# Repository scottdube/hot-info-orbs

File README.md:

# HoT Info Orbs

## Quick start: no software to install on your PC

About 10 minutes. You need the built orbs, a **USB-C data cable** (many cheap
cables carry power only), a computer with **Google Chrome or Microsoft Edge**
(Safari and Firefox cannot talk to USB devices), and a **2.4 GHz** WiFi
network.

1. Download the firmware, **[`info_orbs_fw_combo.bin`](https://github.com/scottdube/hot-info-orbs/releases/download/firmware-1.7.0/info_orbs_fw_combo.bin)**
   (click it; it goes to your Downloads folder). It is also on the
   [firmware release page](https://github.com/scottdube/hot-info-orbs/releases/tag/firmware-1.7.0)
   under **Assets**, with its checksum.
2. In Chrome or Edge, open
   **[ESPConnect](https://thelastoutpostworkshop.github.io/ESPConnect/)**.
3. Plug the orbs into the computer with the USB cable. Click **Connect** (top
   left), pick the port that appeared when you plugged in, and click
   **Connect** in that box. On a Mac it is usually *USB JTAG/serial debug
   unit*; on Windows, *USB Serial Device (COM3)* or another COM number.
4. In the left column click **Flash Tools**. Under **Flash Firmware**:
   - **Firmware binary (.bin):** choose `info_orbs_fw_combo.bin`
   - **Flash offset:** `0x0`
   - click **Flash firmware** and wait for it to finish.
5. Unplug the USB cable and plug it back in. The orbs restart.
6. **WiFi:** the screens show a network named `Info-Orbs_` and two
   characters. Join it on a phone; a setup page opens (if not, browse to
   `http://192.168.4.1`). Pick your home WiFi and type its password.
7. **Your free weather key and time zone:** the orbs show their **IP
   address** when they join your WiFi. On a phone or computer on the same
   WiFi, browse to `http://<that address>/settings`. The page starts with
   **API keys**: paste a [Visual Crossing](https://www.visualcrossing.com/sign-up)
   key, free and about a minute to get. Under **Time zone and location**,
   pick your time zone from the list (it starts on New York; daylight saving
   is automatic) and set your weather town, then press **Save and restart**.
   Until the key is in, the weather page stays empty; the clock works without
   it. Own a Tempest weather station? Its token goes under **API keys** too
   ([details](docs/USER-GUIDE.md#weather-from-your-own-tempest-stations)).

**Connect finds no port?** Put the XIAO in download mode: unplug, hold the
**B** button on the XIAO, plug back in, let go, and click **Connect** again.
Anything else: [Troubleshooting](docs/TROUBLESHOOTING.md).

**Running? Next:** the [user guide](docs/USER-GUIDE.md) covers the buttons,
the pages, the settings page and what the orbs do when WiFi drops.

## Updating later: over WiFi, no cable

After the first install, new versions go in over WiFi with a second, smaller
file, `firmware.bin`. It replaces only the software and keeps your WiFi, key,
settings and start-up picture.

1. Download **[`firmware.bin`](https://github.com/scottdube/hot-info-orbs/releases/download/firmware-1.7.0/firmware.bin)**.
2. On a phone or computer on the same WiFi, browse to
   `http://<orbs' address>/update` (the address the orbs show at start-up).
3. Choose `firmware.bin` and press **Upload**. The orbs restart on their own
   when it is done, with your WiFi, key and settings kept.

**Update failed, or the orbs stay dark?** Nothing is broken: do the
[Quick start](#quick-start-no-software-to-install-on-your-pc) again. It wipes
the board, so WiFi and the weather key go back in at steps 6 and 7.

Want to change the code, or build it yourself? The [build guide](docs/SETUP.md)
covers that.

## Want a more hands-on install? Start here

**You don't need a GitHub account.** The list of folders above is the
project's files. Pick the link that matches what you want:

| You want to… | Go to |
|---|---|
| see what it is and what it does | the [feature sheet](https://scottdube.github.io/hot-info-orbs/features.html), an ordinary web page |
| get a built one running, nothing to install | the [Quick start](#quick-start-no-software-to-install-on-your-pc) above: download one file, flash it from Chrome |
| learn the buttons, the pages and the settings | the [user guide](docs/USER-GUIDE.md) |
| fix something that looks wrong | [Troubleshooting](docs/TROUBLESHOOTING.md), organized by what you see |
| build the software yourself, or change it | the [build guide](docs/SETUP.md), written for someone who has never done this |
| order a bare board | the [board rev 2.5 release](https://github.com/scottdube/hot-info-orbs/releases/tag/board-rev2.5): gerber zip for the fab, parts list, schematic and board PDFs, 3D model |
| print the enclosure | [hardware/enclosures/](hardware/enclosures/): the Winged Speedster enclosure, one `.3mf` per part (they open in Bambu Studio, PrusaSlicer and Orca Slicer), with [how many of each to print](hardware/enclosures/winged-speedster/3mf/README.md), two Bambu Studio projects and the Fusion source |
| get all the source | the green **Code** button above, then **Download ZIP** |

## What it shows

Each page uses all five displays. Set a rotation time (on the settings page,
or `WIDGET_CYCLE_DELAY` in `config.h`) and the orbs move from page to page on
their own. The left and right buttons step back and forward by hand.
Hold the middle button for 2 seconds to see the orb's own info page:
firmware version, WiFi, address, health and data feeds. It appears while
you are still holding. Any button closes it, or it closes by itself after
2 minutes. The [user guide](docs/USER-GUIDE.md) explains every line on it.

- **Clock**: normal, Nixie-tube, or custom faces, in your choice of colors.
- **Weather** for a town (Visual Crossing), from your own
  [Tempest](https://tempest.earth) weather stations (one page per station),
  or both.
- **Stocks**: five tickers.
- **Custom pages** that you set up from the browser, no rebuild:
  - **Web Data** draws a JSON file from any web address.
  - **MQTT**, up to two pages, shows one live value per display from an MQTT
    broker, such as Home Assistant. Long values wrap, and the orbs on a page
    share one text size.

  See [docs/CUSTOM-PAGES.md](docs/CUSTOM-PAGES.md).

## What you need

**To run it** (the [Quick start](#quick-start-no-software-to-install-on-your-pc)):

- The assembled orbs: carrier board, a XIAO ESP32-S3 or S3 Plus, five GC9A01
  round displays, three buttons.
  **S3 or S3 Plus makes no difference to the software.** Both use the same
  file; there is nothing to change. The Plus has more memory, which the
  software does not use yet.
- A **USB data cable**. Many cheap cables carry power only.
- A **2.4 GHz** WiFi network. The ESP32 cannot see 5 GHz.
- A computer with **Google Chrome or Microsoft Edge**, for the first install
  only. After that a phone is enough.
- One free **API key**. An API key is a code a website gives you when you
  sign up, so the orbs can ask it for data. It takes about a minute:
  [Visual Crossing](https://www.visualcrossing.com/sign-up), for weather.
  Sign up for your own. A shared key uses up one free allowance, and if it is
  cancelled it stops working for everyone using it. The time zone needs no
  key: the firmware carries the daylight-saving rules itself.

**To build the software yourself**, also:

- [VS Code](https://code.visualstudio.com) with the
  [PlatformIO](https://platformio.org) extension, and about 1 GB of free
  disk. Most people never need this.

## Using it

Once the orbs are on your WiFi, everything is done from a web browser on a
phone or computer on the same WiFi. The orbs show their **IP address** on
orb 5 when they join (four numbers with dots, like `192.168.1.57`).

| Address | What it does |
|---|---|
| `http://<IP>/settings` | rotation time, which pages show, tickers, weather location and units, time zone, clock face and colors, night dimming, upside-down mounting, the waking eyes at start-up, what to show when WiFi is out, custom pages, your own start-up picture |
| `http://<IP>/update` | install a new version of the software without a cable. The page also shows which version is running. |

The [user guide](docs/USER-GUIDE.md) has the rest: the buttons, each page,
every section of the settings page, the info page, what the amber and red
marks mean, changing WiFi, running from a phone hotspot, and the log.
[Troubleshooting](docs/TROUBLESHOOTING.md) is organized by what you see.

## Building it yourself

[docs/SETUP.md](docs/SETUP.md) is the full walk-through, about 45 minutes the
first time, written for someone who has never used PlatformIO. You make two
settings files (`config.h` for preferences, `secrets.h` for your keys, neither
ever uploaded to GitHub), install over USB once, and update over WiFi after
that. Building it yourself is also how you set a password on the settings and
update pages, and how you
[give each of several sets its own name](docs/SETUP.md#building-more-than-one-set).

## Hardware

*Mainly for people building or changing the board. If you have a kit, you can
skip this section.*

- **Carrier board:** the KiCad 10 project in
  [hardware/hot-info-orbs-xiao-46mm/](hardware/hot-info-orbs-xiao-46mm/), with
  the displays 46 mm apart to fit the enclosure. Its symbol and footprint
  libraries are inside the project, so you can open it without installing
  anything. Its README has the board's history, the pin map and the BOM; the
  files sent to the fab are in its `fab/`.
- **Enclosure:** 3D-printed, in [hardware/enclosures/](hardware/enclosures/);
  design notes in [docs/ENCLOSURE.md](docs/ENCLOSURE.md).
- **Power:** a USB-C cable into the XIAO. The displays run from 5 V and each
  one lowers it to 3.3 V on its own little regulator chip, so the XIAO stays
  cool.
- **Buying displays:** get the round 1.28" GC9A01 display named in the
  [parts list](hardware/hot-info-orbs-xiao-46mm/bom/). If you buy a different
  one, check two things: its pins are in the order VCC, GND, SCL, SDA, DC, CS,
  RST, and the back of the board has a small regulator chip with a capacitor
  on each side.

*For developers:* older boards are not on `main`, but each one is kept under
a tag (`git checkout <tag> -- <folder>` brings a folder back):

| Tag | What |
|---|---|
| [`board-46mm-rev2.5`](https://github.com/scottdube/hot-info-orbs/releases/tag/board-46mm-rev2.5) | the current board as signed off for the fab, with the zips from every earlier fab run |
| [`board-xiao-narrow-final`](https://github.com/scottdube/hot-info-orbs/releases/tag/board-xiao-narrow-final) | first XIAO carrier, displays ~39 mm apart; never ordered |
| [`v1.1-run1`](https://github.com/scottdube/hot-info-orbs/releases/tag/v1.1-run1) | the v1.1 prototype on an ESP32-S3 SuperMini, the module used before the XIAO |

## Documentation

| | |
|---|---|
| [docs/USER-GUIDE.md](docs/USER-GUIDE.md) | using the orbs: buttons, pages, the settings page, the info page, what the orbs do when WiFi drops |
| [docs/TROUBLESHOOTING.md](docs/TROUBLESHOOTING.md) | what to do, organized by what you see |
| [docs/SETUP.md](docs/SETUP.md) | building the software yourself, from an empty computer |
| [docs/CUSTOM-PAGES.md](docs/CUSTOM-PAGES.md) | Web Data and MQTT pages, with Home Assistant recipes (The Villages town squares among them) |
| [docs/TRAPS.md](docs/TRAPS.md) | problems that each cost time once, written down so they don't again |
| [docs/ENCLOSURE.md](docs/ENCLOSURE.md) | the enclosure design and why it looks the way it does |
| [docs/VARIANT-XIAO-ESP32S3.md](docs/VARIANT-XIAO-ESP32S3.md) | why the XIAO, and how the board's pins were chosen |
| [docs/POWER-MEASURED.md](docs/POWER-MEASURED.md) | measured current draw, and why the displays run on 5 V |
| [docs/REQUIREMENTS.md](docs/REQUIREMENTS.md) | requirements for the settings page and WiFi updates |
| [docs/TEMPEST-API.md](docs/TEMPEST-API.md) | how the Tempest weather data is read |
| [docs/DISPLAY-EDGE-TEST.md](docs/DISPLAY-EDGE-TEST.md) | how much of each round display is usable, measured |
| [docs/VARIANT-ESP32-S3-SUPERMINI.md](docs/VARIANT-ESP32-S3-SUPERMINI.md), [docs/ESPHOME-EVALUATION.md](docs/ESPHOME-EVALUATION.md) | history: the module used before the XIAO, and why this isn't an ESPHome project |

Several of these keep the reasoning behind a decision, not just the decision:
a choice with its argument attached can be revisited without starting over.

## Credit and license

**This is a derivative of [Info Orbs by Brett Turner](https://github.com/brettdottech/info-orbs):
his project, his firmware, his idea.** His repository, its
[contributors](https://github.com/brettdottech/info-orbs/graphs/contributors)
and his [assembly and flashing video](https://link.brett.tech/orbsYT) are where
this came from. If you want the original rather than this variant, his boards
can be [bought as a dev kit](https://brett.tech/collections/electronics-projects/products/info-orbs-full-dev-kit).

The firmware is his, with changes. The board is new: a different
microcontroller and a different power layout. The main differences from
upstream:

| | Upstream | This project |
|---|---|---|
| Microcontroller | ESP32 dev kit | Seeed XIAO ESP32-S3 or S3 Plus |
| Display power | 3.3 V from the module's regulator | 5 V, each display regulates its own |
| API keys | in `config.h` | in `secrets.h`, ignored by git; the build fails without it |
| Settings | edit `config.h`, rebuild, reflash | a settings page in the browser |
| Firmware updates | USB cable every time | over WiFi after the first flash |
| Weather | one Visual Crossing town | also your own Tempest stations |
| Custom pages | one MQTT page, laid out with pixel positions | two MQTT pages and a Web Data page, set up on the settings page |

Licensed **AGPL-3.0**, inherited from upstream (see `LICENSE.txt`). If you give
someone a built orb, they are entitled to its source, which is why this
repository is public.

## Contributing

**Found a problem? Tell us.** If a step in one of the guides is wrong or
unclear, or something went wrong in your build, [open an issue](https://github.com/scottdube/hot-info-orbs/issues)
(a GitHub account is needed; it's free). You can also just tell someone at
the club.

*For developers:* fork the repository and open a pull request. Anyone can
clone, build, fork and propose changes without asking. A build that went wrong is worth reporting even if you already got
around it; that is how [docs/TRAPS.md](docs/TRAPS.md) gets written.

**Push access is by invitation** and kept to a few people. That protects the
board files: GitHub gives a personal repository no read-only collaborator
level, so a collaborator can write everything, including KiCad files, which
git cannot merge.

### For collaborators

```bash
git pull --rebase     # before you start
# ...work...
git commit -am "what changed and why"
git push
```

Run `git config pull.rebase true` once, and a plain `git pull` does the right
thing.

**KiCad files cannot be merged.** If two people edit the same `.kicad_pcb`, one
person's work is lost. So say it out loud first: *"I've got the board"* /
*"it's yours"*. Firmware and docs merge normally.

**Don't edit a KiCad project while KiCad has it open**, scripts included. KiCad
writes its in-memory copy back on save and silently discards anything changed
underneath it.

MegaLinter runs on every push and does **not** commit fixes back, so if the
remote has moved, it was a person, not a bot.

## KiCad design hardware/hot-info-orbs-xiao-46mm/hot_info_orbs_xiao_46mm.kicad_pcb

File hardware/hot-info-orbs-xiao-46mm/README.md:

# HoT Info Orbs — XIAO carrier at 46 mm display pitch (KiCad project)

**Copy of `hardware/hot-info-orbs-xiao/` made 2026-10-19 (from branch
`enclosure-front-mockup`, 318e8b0) with one physical change: the five
displays sit 46.0 mm centre to centre instead of ~38.98 mm**, to match the
enclosure front in Fusion (`main_body_front`: bezel centres at
32.75 + n × 46.0; see `docs/ENCLOSURE.md`). The enclosure grows out of this
board; this board is the one going to the fab. The original project left
`main` on 2026-10-25 and is at tag `board-xiao-narrow-final`.

**The board's 3D model is in `3d-pcb-assembly/`** (renamed from `3d-assembly/`
on 2026-11-12). Older entries below that name
`3d-assembly/hot_info_orbs_xiao_assembly.step` describe the narrow board's
export, which is at that tag and not in this folder.

What `tools/pitch_46.py` changed (run once, then `tools/route_xiao.py`):

- DS1–DS5 at x = 57.04 / 103.04 / 149.04 / 195.04 / 241.04 (DS3 unchanged
  and now the board centre). y unchanged.
- Board 224.0 × 47.78 mm (was 198.82 wide): edges x 37.04 … 261.04, 20 mm
  from the outer display centres. y 62.0 … 109.78 as before.
- Seven Ø3.2 holes re-derived by the same rules: corners 5 mm in, mid holes
  at centre ± 19.5 (129.54 / 168.54, top row, plus 168.54 bottom).
- SW1–SW3 at thirds of the new width (centres 111.71 / 149.04 / 186.37), the
  `button` labels with them.
- Back silk: title block keeps its offset from the low-x edge, logo and club
  text keep theirs from the high-x edge; rev text `rev X0.2 · 46 mm pitch`
  (now 2.1, below).
- U2, C1, R1, C2 and the XIAO notes did not move. Schematic unchanged.
- Re-routed from bare copper with Freerouting 2.4.1 (46 nets, 0 unrouted,
  0 violations, 20 passes), GND pour refilled. **DRC 0 errors / 0 warnings /
  0 unconnected / 0 parity** (2026-10-19).

Outputs of that pass: `fab/hot_info_orbs_xiao_46mm_X0.2_run1_gerbers.zip`
(superseded the same day, see `fab/README.md`).

## Grown 5 mm at the top (2026-10-19, `tools/grow_top.py`, rev 2.1)

Placed in the Fusion `overall assembly`, the X0.2 board's top mounting holes
sat 5 mm too low for a standoff post at either end of the top row: the
enclosure's top lip was in the way, so the ends hung from corner hangers
instead. The board cannot shift on the enclosure (the five displays are
pinned by the bezel holes) and the sockets fix the bottom edge, so the TOP
edge was grown 5 mm instead. Run once after `pitch_46.py`, then
`tools/route_xiao.py 20` again:

- Board **224.0 × 52.78 mm**, y 57.0 … 109.78 (was 62.0 … 109.78).
- Top-row holes up 5 mm to y 62.0 (x 42.04 / 129.54 / 168.54 / 256.04);
  bottom row unchanged. All seven still 5 mm from an edge.
- SW1–SW3 up 5 mm (y 59.59), so the actuators clear the enclosure's top lip
  by less: 12.9 mm plunger gap, was 17.9. The `button` labels went with them.
- GND pour rebuilt to the new edge. Displays, XIAO, passives, logo and title
  block did not move.
- Rev silk **`rev 2.1 · 46 mm pitch`** (Scott set the number 2026-10-19; it
  read X0.3 for a few minutes, never fabbed).
- Re-routed from bare copper: 46 nets, 0 unrouted, 0 violations, 300
  tracks+vias (6 vias). **DRC 0 errors / 0 warnings / 0 unconnected /
  0 parity.**

Outputs: `fab/hot_info_orbs_xiao_46mm_2.1_run1_gerbers.zip` (see
`fab/README.md`), `fab/46mm_top.png` / `fab/46mm_bottom.png`, and
`3d-pcb-assembly/hot_info_orbs_xiao_46mm_assembly.step` (same export recipe as
below; all six models resolve). That STEP is what `main_body_front` v4 and
`overall assembly` v4 were built against (`docs/ENCLOSURE.md`); rev 2.3
below overwrote it.

## Rev 2.3: XIAO 4 mm toward the bottom edge (2026-10-20, `tools/lower_xiao.py`)

Scott wants the USB-C jack as close to the enclosure wall as the board allows
without growing the board or crowding the socket pins against the edge; he
eyeballed 2-4 mm and the numbers allow the top of that range. Run once after
`grow_top.py`, then `tools/route_xiao.py 20` again:

- **U2 down 4.0 mm** to y 99.0. Lowest socket pads at y 106.62: pad copper
  2.31 mm from the edge (the display socket pads are 2.95 mm from it; the
  rule is 0.5). Socket housings end 1.89 mm inside the edge, the module body
  0.92 mm inside it, and the USB-C face (1.5 mm proud of the body) lands
  0.6 mm **past** the edge, at the wall. The F.Silk "XIAO goes on other
  side" rectangle moved with it and is clipped 0.5 mm inside the edge; the
  footprint's own USB-C silk crosses the edge and is left alone (3 DRC
  `silk_edge_clearance` warnings; the fab trims silk outside the outline).
- **C1 could not follow it down**: DS3's back-side pin labels sit at y 101.9
  and C1's courtyard was already 0.4 mm above them on 2.1 (a 2.4 mm drop put
  the 5V pad on the "DC" label, 3 silk warnings). So C1 keeps y 99.02 and
  moves **3.2 mm sideways to x 143.99**, courtyard 0.5 mm from the XIAO
  socket's, giving up the 3 mm "castellation pad" margin of 2026-10-17.
  Pad to pad the 5V run is 9.25 mm, the same as 2.1: the XIAO moved away
  from C1 by as much as C1 moved toward it. Anything shorter needs DS3's
  back-silk labels moved or C1 under the module (cap height unverified).
- **C2 and R1 swapped**, one column at x 143.99: C2 (1 µF reset cap) straight
  above C1 with its GND pad lowest (y 92.73, beside C1's GND at 96.52), R1
  above C2 with its RST pad lowest (85.04, adjacent to C2's RST at 87.73),
  3V3 pad at 74.88. The long run is the 3V3 feed, not the reset node.
  Courtyard gaps 0.5 mm; reference labels in a column 4.6 mm to the right.
- Rev silk **`rev 2.3 · 46 mm pitch`**; title-block rev 2.3 in both the
  schematic and the board (they read X0.1 / 1.1 before). **There is no 2.2**;
  Scott named this 2.3.
- Re-routed from bare copper: 46 nets, 0 unrouted, 0 violations, 284
  tracks+vias (14 vias). **DRC 0 errors / 3 warnings (the USB-C silk over
  the edge, above) / 0 unconnected / 0 parity.** `route_xiao.py` now reruns
  Freerouting when a pass ends "stage interrupted" with a non-empty SES
  (seen once: 44 unrouted after 0.14 s, the same DSN routed clean by hand).

**Run 2, same day (`tools/stitch_islands.py`):** Scott spotted two wide bare
bands in the back pour, SW2 down past R1 to the XIAO and DS1 to DS2 along
the bottom edge. Measured (fill redone in memory with island removal off):
removed islands of 283 and 211 mm², copper boxed in by the SW2/SW3 pair and
the 3V3 feed, and by the DS1 CS1/SCLK/MOSI bundle and the shared RST track.
Removing them is right (floating copper beside SPI lines), so the fix is a
connection: **the GND zone now pours F.Cu as well**, and a 0.8/0.3 GND via
sits in each island (68.70,101.46 and 143.10,68.13). Vias alone did nothing:
with no front copper the island plus via was still floating and KiCad still
removed it. DS5's GND pin gets 45° thermal spokes on the front (the +5V front
track along the bottom blocks its downward spoke; the rule wants two). DRC
0 / 3 / 0 / 0 as before; 16 vias. **ERC 0 / 0**: the six
`lib_symbol_mismatch` warnings were the project libraries still naming the
PINS/DIP footprints as the symbols' default while the schematic's embedded
copies (what the board was built from) name the SOCKET ones; the library
files now say SOCKET, the schematic is untouched.

**Run 3 (`tools/ds_refs.py`, 2026-10-20 17:44): the DS1–DS5 designators are
on the back silk**, 1.5 mm text mirrored behind each display socket (y 103.3,
glyphs 0.8 mm above the pad copper, 0.58 mm below the footprint's back
outline). They had been on the front silk at y 109.03 with their bottom
0.015 mm from the board edge: the fab trims silk outside the outline and
the display module covers that strip once plugged in, so a built board
had no readable socket name. Scott's ask: visible for troubleshooting with
beginners. Nothing else moved: run 3's copper, mask, outline and drill
differ from run 2 only by their timestamp lines. DRC unchanged (0 / 3 / 0 / 0).
Yang got this STEP (link and file) by email the same evening; his previous
copy was rev 2.1.

**Rev 2.4 (`tools/display_marks.py`, 2026-10-20 19:05): a front-silk circle
with the word Display at each module position.** Ø29.5 mm, line 0.2, text
2.0 mm, centered on each display's 3D-model origin (x 58.74 + n·46, y 81.0).
A bare board had shown five socket rows and a "XIAO GOES ON OTHER SIDE"
box, nothing saying which face the displays plug into. The circle is
smaller than the lit area (Ø32.5) because at DS3 a lit-area circle crosses
the front annular rings of C1 and XIAO pad 8 (two DRC "clipped by solder
mask" warnings, two fab-cut gaps in the ring); 14.75 mm is the largest
radius that clears them. The DS3 circle crosses the XIAO box's corner,
which is the truth of the layout. Scott had the rev bumped for it (silk and
title block, schematic rev too). Copper, mask, outline and drill are run 3's
(diffed: timestamp and rev-attribute lines only). DRC 0 / 3 / 0 / 0.

Outputs: `fab/hot_info_orbs_xiao_46mm_2.4_run1_gerbers.zip` (the 2.3 runs
are superseded, see `fab/README.md`),
`fab/46mm_top.png` / `fab/46mm_bottom.png`, and
`3d-pcb-assembly/hot_info_orbs_xiao_46mm_assembly.step` (rev 2.4 silk).
`overall assembly` **v8** (2026-10-20 evening) holds this STEP, same
transform as before, pose captured as Position6; it also carries the
bezel and watch-crystal occurrences that were sitting unsaved in the
session. `main_body_front` v4 has **no USB cutout yet** (an
earlier line here said one was "4 mm off"; it never existed); the jack's
place in the enclosure is measured in `docs/ENCLOSURE.md`.

## Rev 2.5: probe pads for 3V3, GND and 5V (2026-10-25, `tools/test_points.py`)

Scott wanted test pads for debugging other people's builds. RST, SCLK,
MOSI, DC and CS1–CS5 pads were suggested; his call was "just add gnd 3.3v
and 5v".

- **Board:** TP1 3V3, TP2 GND, TP3 5V. One column at x 173.74, midway
  between the DS3 and DS4 display circles, at y 78.46 / 81.00 / 83.54
  (2.54 mm pitch, so a 1x3 header or a 3-pin clip fits). GND is in the
  middle: the black probe stays put and the red one reaches either rail.
  Each is a 2.0 mm plated pad on a 1.00 mm drill. That is the drill the
  sockets already use, so there is no new drill size. Plated through, so
  they can be probed from either face.
  - Silk: the rail names beside each pad and a box round the column, on
    both faces. Run 2 (`tools/test_label.py`) adds "Test" on the other
    side of the column from the rail names, on each face, first set
    vertically along the column. Scott rotated both to horizontal at the
    GND row in KiCad (run 3: front x 170, back x 177). Copper is
    unchanged, so there was no reroute. In the 3D render the DS3 module
    covers the front "T", just as DS4 covers the front rail names. The
    back face is the one that stays readable with displays fitted.
  - With the modules plugged in, the pads stay clear in the gap, about
    2.5 mm from each module edge. The front labels end up under DS4's
    module, but the back labels are always readable.
  - Rejected: the gap next to DS3 at x ~153, where the pads clipped DS3's
    front silk circle; and a 1x8 row with the bus signals (Scott's call
    above).
- **Footprint:** `lib/_TestPoints.pretty/TestPoint_THTPad_D2.0mm_Drill1.0mm_P2.54`
  is the stock KiCad `TestPoint_THTPad_D2.0mm_Drill1.0mm` trimmed so three
  can sit at 2.54 mm pitch:
  - courtyard r 1.5 → 1.25 (the stock courtyards overlapped: 2 DRC errors);
  - no silk circle (the circles touched);
  - reference on F.Fab (on silk it sat on the next pad).

  Editing the stock footprint inside the board was rejected because it
  leaves three `lib_footprint_mismatch` warnings for good.
- **Schematic:** TP1–TP3 (`Connector:TestPoint`) go in a dashed "TEST POINTS"
  box in the bottom housekeeping row, right of POWER FLAGS, with its top
  aligned at y 160.02. They are wired the way POWER FLAGS is: the power
  symbol and the TP sit on the same point, and 3V3 is joined by its local
  label.
  - **Not in the BOM:** `in_bom no`, and the footprint is
    `exclude_from_bom`. A test pad is a bare hole, so there is nothing to
    buy and the kit cost does not change. Checked: `kicad-cli sch export
    bom` lists no TP.
- **Rerouted from bare copper:** Freerouting finished with 49 nets,
  0 unrouted and 0 violations, at 10, 20 and 30 passes alike.
  - **C2 pad 2 (GND):** /MOSI now runs round it on three sides on B.Cu, so
    the back pour reaches it with one spoke instead of two (a
    `starved_thermal` error). It still has its own 0.35 mm GND track on
    B.Cu and full spokes on F.Cu. `hot_info_orbs_xiao_46mm.kicad_dru` lets
    that one pad pass with one spoke; every other thermal still needs 2.
    Checked: the same rule aimed at pad 1 brings the error back.
  - A DRC exclusion was rejected: the key carries the marker position and
    item UUIDs, three guesses at the format did not match, and a reroute
    would invalidate it anyway.
  - **No stitching vias this time.** The reroute removed rev 2.4's three
    GND vias (Freerouting's one, plus the two from `stitch_islands.py`).
    Measured by filling with island removal off and on: the back pour now
    loses no island at all. The region at x 138–184 is joined to GND
    through TP2's and C2's pads. The front loses only the sub-100 mm²
    slivers between socket pins, as before. So `stitch_islands.py` was
    not rerun; its assertion of exactly two islands would fail anyway.
- **DRC:** 0 errors, 3 warnings (the same USB-C silk warnings on U2),
  0 unconnected, 0 parity. **ERC:** 0.

Outputs:
- `fab/hot_info_orbs_xiao_46mm_2.5_run1_gerbers.zip`. Drill T4 (1.00 mm)
  goes from 49 to 52 hits; vias go from 16 to 13, all signal.
- `fab/46mm_top.png` / `fab/46mm_bottom.png`.
- `3d-pcb-assembly/hot_info_orbs_xiao_46mm_assembly.step`.
- The rev reads 2.5 in the back silk, the board title block and the
  schematic title block.

Not updated: `overall assembly` in Fusion still holds the 2.4 STEP. The
probe pads add no height.

## Schematic layout (2026-10-24, Scott's arrangement)

The displays became a labeled block (`tools/display_block.py`, 101a0ba)
and every circuit group got a dashed, titled box (`tools/group_boxes.py`,
ade894a). Those boxes were fitted around wherever the parts happened to
sit, so the page came out scattered: boxes at five different heights, the
MCU down against the title block. Scott found it "not pleasing to the
eye" and rearranged it himself. **His arrangement is the layout rule for
this sheet, and in his words symmetry is the key difference:**

- **Symmetry.** Each group sits centered in its box with even margins.
  Measured from the render: about 3–4 mm left, right, top and bottom on
  BUTTONS, MCU, 5V BULK and POWER FLAGS, against the lopsided margins the
  fitted boxes had. The exceptions are forced by text. DISPLAY RESET is as
  wide as its title, so its content sits left. DISPLAYS has its socket
  field text on the left.
- **Rows, not scatter.** Row 1 is the DISPLAYS block, full width. Row 2
  holds every functional block, **tops aligned on one line** (y 87.63) with
  ragged bottoms. Each box is only as tall as its contents.
- **Signal order, left to right:** BUTTONS (inputs), then MCU, then
  DISPLAY RESET, then 5V BULK. That reads as inputs → processor → what
  feeds the displays.
- **Shared left margin.** BUTTONS starts at the DISPLAYS box's left edge
  (x 16.51).
- **Housekeeping out of the circuit rows.** POWER FLAGS (ERC only) sits
  at the bottom left, clear of the title block. Since rev 2.5, TEST POINTS
  sits beside it with its top aligned at y 160.02.
- Boxes hug their contents; the title goes inside the bottom-left corner.

Netlist identical to ade894a (names, pins, components), ERC 0.
`group_boxes.py` sizes boxes from content but does not arrange them.
**Re-running it over this layout would resize Scott's boxes and lose the
aligned tops**, so move parts and boxes by hand in eeschema instead.

The rest of this README is inherited from the parent project. Its y
coordinates and the pin map still hold; its x coordinates and board width
describe the narrow board.

---

# HoT Info Orbs — XIAO ESP32-S3 variant (KiCad project)

Carrier for five GC9A01 displays and three buttons, taking a **Seeed Studio
XIAO ESP32-S3 or XIAO ESP32-S3 Plus** (SKU 102010671), the builder's choice; the two
share the edge pins. This is the project's only board. It was copied on
2026-10-14 from the v1.1 prototype board, built for an ESP32-S3 SuperMini
(`hardware/hot-info-orbs/` at tag `v1.1-run1`, the boards ordered
2026-08-29); that module is not part of the project.

**S3 and S3 Plus are interchangeable here** (Seeed wiki, checked 2026-10-14):
identical D0–D10 → GPIO map, user LED GPIO21 on both, 21 × 17.8 mm both,
U.FL antenna both, 8 MB PSRAM both. Flash 8 MB vs 16 MB; the firmware builds
for 8 MB and uses all 8 MB, so one binary runs on either. The Plus's extra
D11–D19 are on its back and are not used by this board.

**Antenna:** the XIAO has a U.FL pigtail and a stick-on FPC antenna (Seeed
A-02, inventory part 102), and **the antenna is not mounted on this board**
(Scott, 2026-10-16), so the board has no copper keepout for it. The
2026-10-14 `ANTENNA_PATCH` rule area is removed; `tools/antenna_patch.py` is
retired and kept as history.

**Physical layout (2026-10-16/17, `tools/physical_rework.py`; routed 2026-10-17):**
- Displays plug in: each GC9A01 keeps its male header and seats in a 1x07
  2.54 mm female socket (footprint `_Displays:GC9A01_SOCKET`, same pads as
  `GC9A01_PINS`, display lifted 8.5 mm in 3D). Pad row at y 105.98, as low as
  the 0.5 mm copper-to-edge rule allows.
- Board top edge raised 17.28 mm to y 62.0, even with the tops of the
  displays (measured off a render); top mounting holes and the GND pour
  moved up with it. Bottom edge 2 mm lower (2026-10-17) to route under the
  display pin rows; the bottom holes followed it, so all seven are 5 mm in.
  Board is now 198.82 x 47.78 mm.
- Back silk: HOT hand logo, "The Villages / Hands-On Tech Club" and
  handsontech.org (the club's domain; it 301s to the weebly host).
- C1, C2, R1 and SW1-3 are on the BACK, the XIAO's side (Scott: "all on
  the same side as the xiao").
- Buttons: right-angle 6 x 6 x 8 mm tact switches (uxcell, Amazon) on the TOP
  edge, actuators out past it, centred on the board's 1/3 line, its 2/3
  line and midway: x 117.64 / 150.77 / 183.91. Footprint is KiCad's stock
  `SW_Tactile_SPST_Angled_PTS645Vx39-2LFS` - **unverified for the uxcell
  part**: the listing says 6.5 mm and 4.5 mm pin pitch, the footprint has
  4.5 mm (switch pins) and 7.0 mm (mounting tabs). Measure one.
- XIAO plugs in like the displays: male headers into two 1x07 female
  sockets (footprint `_ESP32 modules:XIAO-ESP32-S3-SOCKET`, holes at the
  header positions +-7.62 mm, 1.0 mm drill; module 11 mm off the board in 3D,
  with the male headers modelled under it, upside down, plastic on the sockets).
- C1 (+5V bulk for the displays) right beside the XIAO's 5V/GND pins;
  R1 + C2 (display RC reset) in the same column above it, R1 off the 3V3
  pin. Pass 1 had them in the bottom-edge gaps between sockets, ~36 mm
  from the 5V pin. The column sits 8.5 mm out from the pins, leaving 3 mm
  beside the XIAO free for castellation pads if we ever solder it down.
- White solder mask, black silkscreen (stackup colors; order the same at the fab).
- Board ID is on the back: a 28 mm HOT hand logo (`_Logos:Hot_Logo_28mm`,
  the 5 mm logo's polygons scaled) with "The Villages / Hands-On Tech Club"
  at one end; "HoT Info Orbs", "XIAO ESP32-S3 · rev X0.1" and the
  brettdottech credit at the other, in Comic Sans as on v1.1.
- Mounting holes: the four corner holes moved 2 mm in on each axis (now
  5 mm from each edge: x 56.37 / 245.18, y 67.0 / 102.78), plus two
  mid-board holes on the top row at x 131.28 and 170.27 (centre +-19.5 mm,
  in the gaps above DS2/DS3 and DS3/DS4; 22.5 mm from each display centre
  against a 16.2 mm display radius). Not on the bottom row: the XIAO, its
  sockets and the display socket row are there. A seventh hole on the
  bottom row straight below the right mid hole (170.27, 102.78), DS3/DS4
  gap, about 6 mm from each display tab; its left twin would hit the XIAO.

## Status — ROUTED (2026-10-17)

`tools/route_xiao.py`, one Freerouting pass, then DRC with refilled zones:
0 errors, 0 warnings, 0 unconnected, 0 parity (re-routed after the club URL,
bottom holes and upright DS labels: 314 tracks+vias). STEP in `3d-pcb-assembly/` now
carries tracks, pads and the pour. BOM: `bom/hot_info_orbs_xiao_bom.xlsx`
(and `.csv`), generated by `tools/make_bom.py`; C1 is 100 uF 16 V (set 2026-10-17).
BOM carries Link 1 prices and a build-cost total. Nothing ordered, nothing flashed.

### 2026-10-14 (superseded)

Schematic ERC 0; board autorouted, DRC 0 errors / 0 unconnected / 0 parity
(14 silk warnings = Seeed's module outline over its own pads, accepted).
Firmware env `xiao-esp32s3` compiles. Nothing ordered, nothing flashed.
3D: every footprint resolves its model (Seeed's XIAO ESP32S3 PLUS STEP on U2,
the GC9A01 STEP on DS1–DS5, both project-local under `lib/3d/`), and the board
assembly is exported to `3d-assembly/hot_info_orbs_xiao_assembly.step`
(2026-10-14). `docs/HANDOFF.md` has the step log and the traps;
`../../docs/VARIANT-XIAO-ESP32S3.md` has the reasoning.

## Regenerating the board

All with KiCad CLOSED. `tools/swap_to_xiao_sch.py` and `tools/merge_xiao_pads.py`
were run once and their results are committed; do not rerun them. The board
itself is reproducible from the v1.1 copy of the .kicad_pcb (commit e6ea813):
`tools/swap_to_xiao_pcb.py` (KiCad's Python) then `tools/route_xiao.py`
(Freerouting headless, ~5 s, ends with a DRC + parity count). Each script's
docstring says why it does what it does.

## Module fit

Only the 14 castellated edge pins are used, so the footprint
(`_ESP32 modules:XIAO-ESP32-S3-DIP`, Seeed's own, CC BY-SA 4.0, with each pin's
PTH + castellation pad pair merged into one oval through-hole pad — see
`tools/merge_xiao_pads.py`) takes the module on 2.54 mm headers **or** soldered
flat on its castellations. Any XIAO ESP32-S3
(plain, Sense, Plus) has the same 14 edge pins and fits; the Plus's nine extra
pads under the module are not used.

## Pin map (decided 2026-10-14; same for S3 and S3 Plus)

11 GPIOs are available on the edge; the SuperMini board used 12, so the
display RST line moves off the MCU onto an RC power-on reset (R1 10 kΩ to
3V3, C2 1 µF to GND) and the firmware uses TFT_eSPI's software reset
(`TFT_RST -1`). The BUSY indicator goes to the XIAO's on-board user LED
(GPIO21, active LOW), which is not an edge pin.

| XIAO pin | GPIO | Signal | Note |
|---|---|---|---|
| D0 | 1 | SW1 (left) | same GPIO as the SuperMini board |
| D1 | 2 | SW2 (OK) | same GPIO as the SuperMini board |
| D2 | 3 | DS1 CS | strapping pin (JTAG select); MCU-driven output, no external pull, so harmless |
| D3 | 4 | DS2 CS | |
| D4 | 5 | DS3 CS | |
| D5 | 6 | SW3 (right) | |
| D6 | 43 | DS4 CS | UART0 TX: ROM boot log toggles it before init, harmless on a CS |
| D7 | 44 | DS5 CS | UART0 RX: pulled up at boot, so CS idles high |
| D8 | 7 | SCLK | |
| D9 | 8 | DC | |
| D10 | 9 | MOSI | |
| 5V | — | +5V | displays run from 5 V through their own regulators |
| GND | — | GND | |
| 3V3 | — | 3V3 | button pull side + RST pull-up |

Buttons stay on D0/D1/D5 rather than the UART pins: a button held through a
reset would short 3V3 into GPIO43 while the ROM is driving it.

## Libraries

Project-local, as in the parent project. Added here:

| Nickname | Provides | Source |
|---|---|---|
| `_Seeed XIAO` | `XIAO-ESP32-S3-edge` symbol (Seeed's 25-pin symbol trimmed to the 14 edge pins, so PCB parity has no pad-less pins) | Seeed `OPL_Kicad_Library`, CC BY-SA 4.0 |
| `_ESP32 modules` | `XIAO-ESP32-S3-DIP` footprint, 14 oval THT pads (hole at the header position, copper out to the castellation edge) | same, modified |
| `lib/3d/_ESP32 modules/XIAO-ESP32S3-PLUS-v4.step` | U2's 3D model (Seeed assembly "XIAO ESP32S3 PLUS_V1.0_241025"), attached by `tools/xiao_model.py` (offset (-1.778, -7.62, 0) / rotate (-90, 0, 0), found by rendering against the DIP footprint). In the SOCKET footprint the offset is (-1.651, -6.13, 11): the old fit left the module's holes 1.49 mm off the header pins, measured in Fusion 2026-10-16. Also stands in for the plain S3 (same outline, same USB end). | Seeed product page download, 2026-10-14 |

The SuperMini symbol/footprint are still in `lib/` but unused.

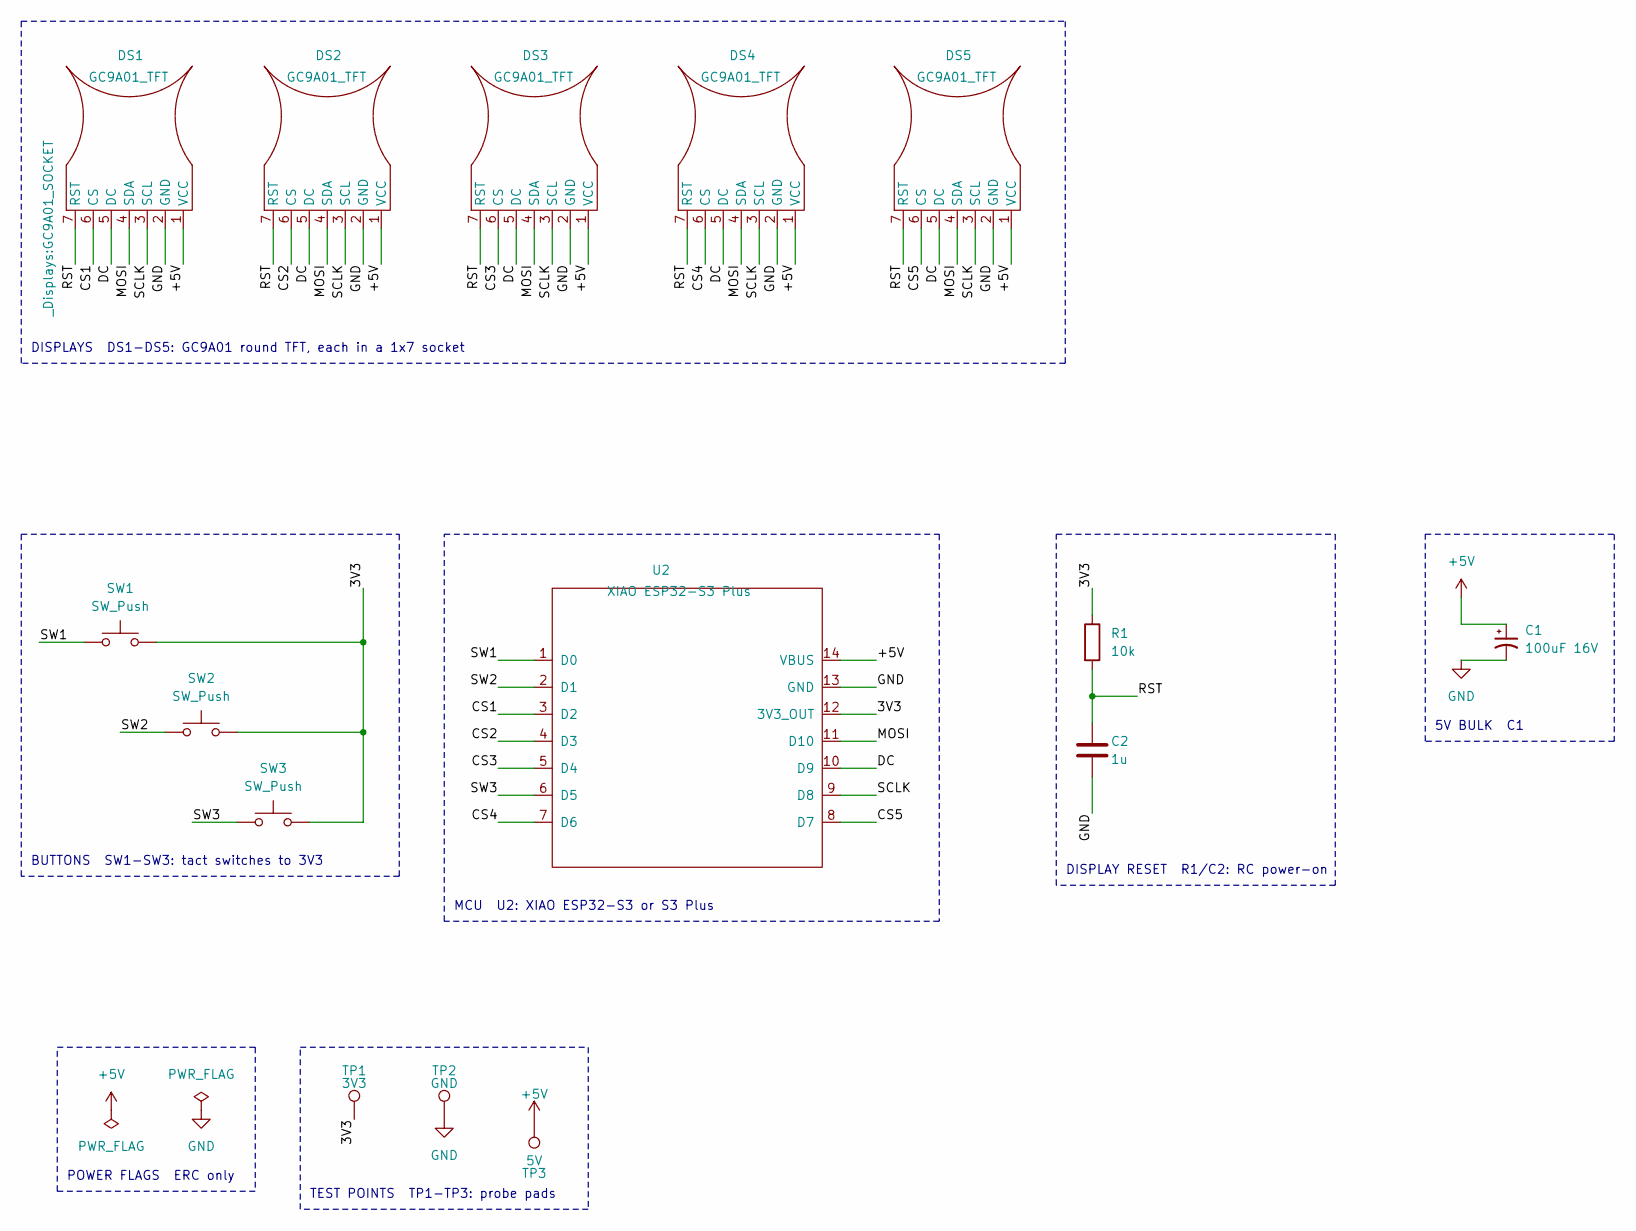
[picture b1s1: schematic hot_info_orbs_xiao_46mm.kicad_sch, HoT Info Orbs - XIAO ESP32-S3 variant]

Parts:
C1: 100uF 16V; CP_Radial_D6.3mm_P2.50mm
C2: 1u; C_Disc_D5.0mm_W2.5mm_P5.00mm
DS1, DS2, DS3, DS4, DS5: GC9A01_TFT; GC9A01_SOCKET
R1: 10k; R_Axial_DIN0207_L6.3mm_D2.5mm_P10.16mm_Horizontal
SW1, SW2, SW3: SW_Push; SW_Tactile_SPST_Angled_PTS645Vx39-2LFS
TP1: 3V3; TestPoint_THTPad_D2.0mm_Drill1.0mm_P2.54
TP2: GND; TestPoint_THTPad_D2.0mm_Drill1.0mm_P2.54
TP3: 5V; TestPoint_THTPad_D2.0mm_Drill1.0mm_P2.54
U2: XIAO ESP32-S3 Plus; XIAO-ESP32-S3-SOCKET

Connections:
+5V: C1.1, DS1.1 (VCC), DS2.1 (VCC), DS3.1 (VCC), DS4.1 (VCC), DS5.1 (VCC), TP3.1, U2.14 (VBUS)
/3V3: R1.1, SW1.2, SW2.2, SW3.2, TP1.1, U2.12 (3V3_OUT)
/CS1: DS1.6 (CS), U2.3 (D2)
/CS2: DS2.6 (CS), U2.4 (D3)
/CS3: DS3.6 (CS), U2.5 (D4)
/CS4: DS4.6 (CS), U2.7 (D6)
/CS5: DS5.6 (CS), U2.8 (D7)
/DC: DS1.5 (DC), DS2.5 (DC), DS3.5 (DC), DS4.5 (DC), DS5.5 (DC), U2.10 (D9)
/MOSI: DS1.4 (SDA), DS2.4 (SDA), DS3.4 (SDA), DS4.4 (SDA), DS5.4 (SDA), U2.11 (D10)
/RST: C2.1, DS1.7 (RST), DS2.7 (RST), DS3.7 (RST), DS4.7 (RST), DS5.7 (RST), R1.2
/SCLK: DS1.3 (SCL), DS2.3 (SCL), DS3.3 (SCL), DS4.3 (SCL), DS5.3 (SCL), U2.9 (D8)
/SW1: SW1.1, U2.1 (D0)
/SW2: SW2.1, U2.2 (D1)
/SW3: SW3.1, U2.6 (D5)
GND: C1.2, C2.2, DS1.2 (GND), DS2.2 (GND), DS3.2 (GND), DS4.2 (GND), DS5.2 (GND), TP2.1, U2.13 (GND)

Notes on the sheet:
MCU U2: XIAO ESP32-S3 or S3 Plus
5V BULK C1
POWER FLAGS ERC only
DISPLAYS DS1-DS5: GC9A01 round TFT, each in a 1x7 socket
BUTTONS SW1-SW3: tact switches to 3V3
DISPLAY RESET R1/C2: RC power-on
TEST POINTS TP1-TP3: probe pads

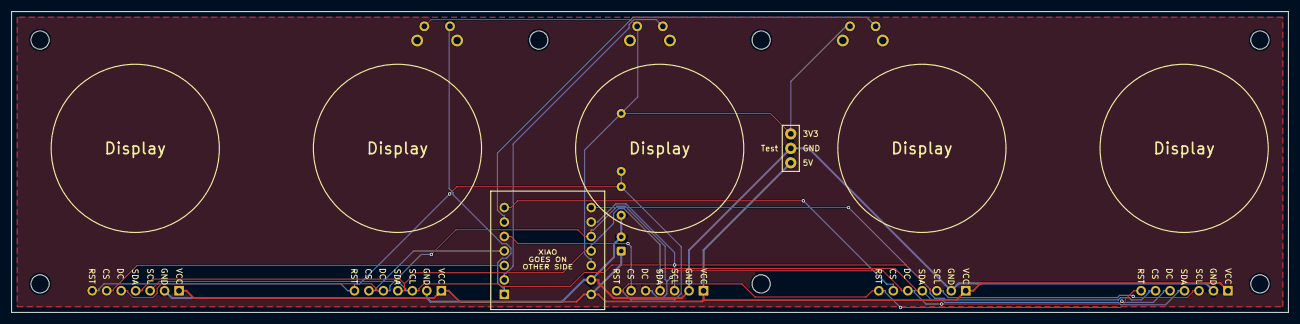
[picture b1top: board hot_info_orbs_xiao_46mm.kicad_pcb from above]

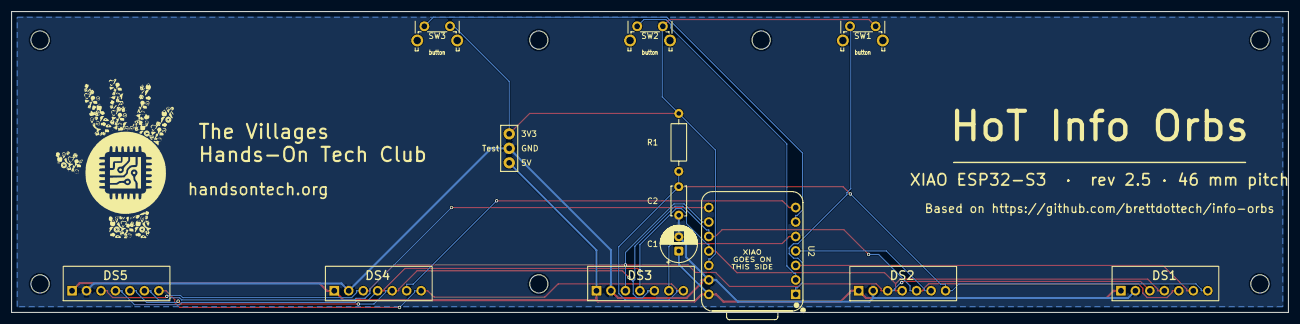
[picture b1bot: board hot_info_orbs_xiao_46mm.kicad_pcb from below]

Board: 2 copper layers, 224.0 x 52.8 mm, 15 parts (7 on the bottom side), 15 nets.

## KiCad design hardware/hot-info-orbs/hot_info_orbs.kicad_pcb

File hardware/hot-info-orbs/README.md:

# HoT Info Orbs — KiCad project

> **Prototype, not the club board.** The club board takes a XIAO ESP32-S3 or
> XIAO ESP32-S3 Plus and is in
> [`hardware/hot-info-orbs-xiao/` on the `xiao-esp32s3-plus` branch](https://github.com/scottdube/hot-info-orbs/tree/xiao-esp32s3-plus/hardware/hot-info-orbs-xiao).

ESP32-S3 SuperMini carrier for five GC9A01 displays. Original board by Yangmin
Shen, KiCad 10, received 2026-08-28.

## Libraries are project-local, on purpose

The custom symbols and footprints live in `lib/` and are wired up through
`sym-lib-table` and `fp-lib-table` using `${KIPRJMOD}`. **Do not move them into
your global KiCad libraries.** Clone the repo, open the project, and everything
resolves with no setup.

This is deliberate. Upstream's board (`PCBFiles+Schematics/Main PCB`) references
libraries named `A Local Libs` and `New folder` that exist only on its author's
machine — the footprints render because KiCad caches them inside the board file,
but nobody else can place a new instance or update one. Project-local tables
avoid that permanently.

| Nickname                 | Provides                     |
|--------------------------|------------------------------|
| `_AZDelivery components` | `GC9A01_TFT` symbol          |
| `_ESP32 modules`         | SuperMini symbol + footprint |
| `_Displays`              | `GC9A01_PINS` footprint      |
| `_Logos`                 | `Hot_Logo_5x5mm` footprint   |

**`_Logos` was not in the zip.** It was recovered by extracting the embedded
footprint from `hot_info_orbs.kicad_pcb`, since KiCad caches full definitions in
the board file. It is byte-equivalent to what the board already places, but it
has not been round-tripped through the footprint editor — if it misbehaves, ask
Yang for the original.

`.kicad_prl` is deliberately not committed: it is per-user editor state
(open tabs, zoom, last-used layer) and only creates conflicts.

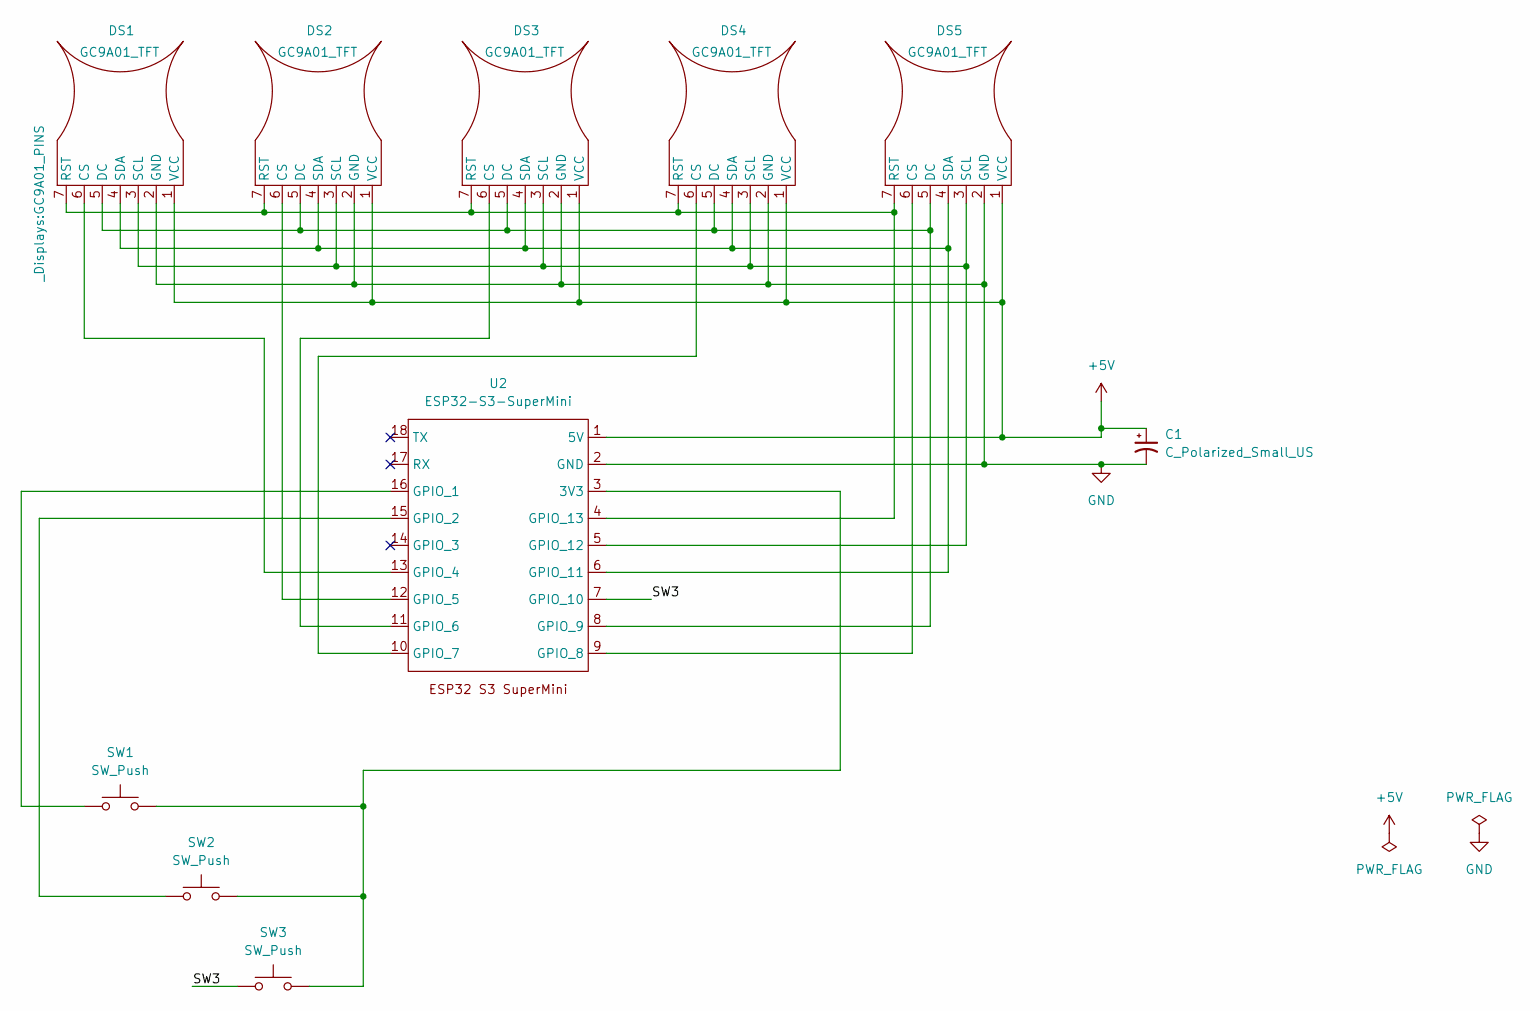
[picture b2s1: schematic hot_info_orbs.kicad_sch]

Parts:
C1: C_Polarized_Small_US; CP_Radial_D6.3mm_P2.50mm
DS1, DS2, DS3, DS4, DS5: GC9A01_TFT; GC9A01_PINS
SW1, SW2, SW3: SW_Push; SW_PUSH_6mm_H5mm
U2: ESP32-S3-SuperMini; ESP32S3-SuperMini

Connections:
+5V: C1.1, DS1.1 (VCC), DS2.1 (VCC), DS3.1 (VCC), DS4.1 (VCC), DS5.1 (VCC), U2.1 (5V)
/SW3: SW3.1, U2.7 (GPIO_10)
GND: C1.2, DS1.2 (GND), DS2.2 (GND), DS3.2 (GND), DS4.2 (GND), DS5.2 (GND), U2.2 (GND)
unnamed: DS1.6 (CS), U2.13 (GPIO_4)
unnamed: DS1.5 (DC), DS2.5 (DC), DS3.5 (DC), DS4.5 (DC), DS5.5 (DC), U2.8 (GPIO_9)
unnamed: DS1.7 (RST), DS2.7 (RST), DS3.7 (RST), DS4.7 (RST), DS5.7 (RST), U2.4 (GPIO_13)
unnamed: DS1.3 (SCL), DS2.3 (SCL), DS3.3 (SCL), DS4.3 (SCL), DS5.3 (SCL), U2.5 (GPIO_12)
unnamed: DS1.4 (SDA), DS2.4 (SDA), DS3.4 (SDA), DS4.4 (SDA), DS5.4 (SDA), U2.6 (GPIO_11)
unnamed: DS2.6 (CS), U2.12 (GPIO_5)
unnamed: DS3.6 (CS), U2.11 (GPIO_6)
unnamed: DS4.6 (CS), U2.10 (GPIO_7)
unnamed: DS5.6 (CS), U2.9 (GPIO_8)
unnamed: SW1.2, SW2.2, SW3.2, U2.3 (3V3)
unnamed: SW1.1, U2.16 (GPIO_1)
unnamed: SW2.1, U2.15 (GPIO_2)

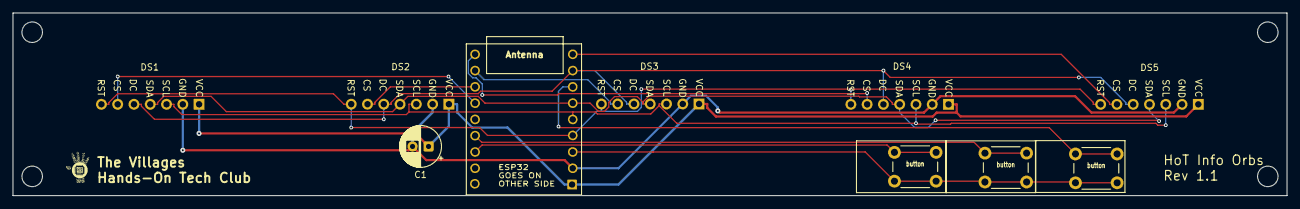
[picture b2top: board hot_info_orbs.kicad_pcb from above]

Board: 2 copper layers, 198.8 x 28.5 mm, 10 parts (1 on the bottom side), 15 nets.
